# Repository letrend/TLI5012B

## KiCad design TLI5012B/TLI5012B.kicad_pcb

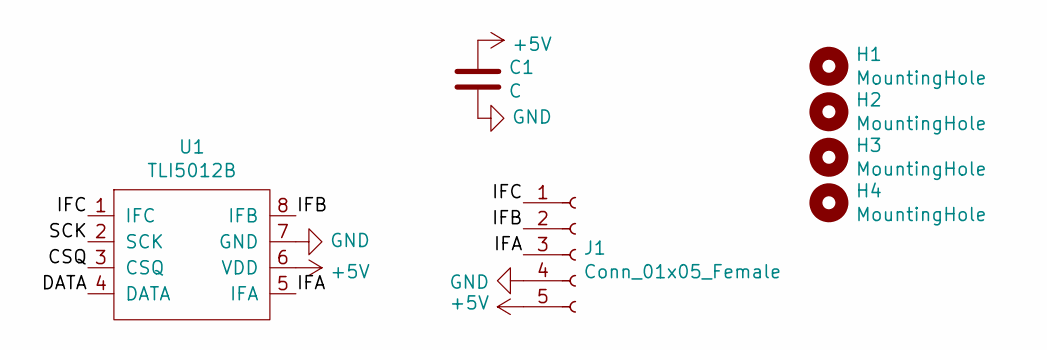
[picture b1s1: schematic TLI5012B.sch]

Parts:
C1: C; C_0402_1005Metric
H1, H2, H3, H4: MountingHole; MountingHole_3.2mm_M3
J1: Conn_01x05_Female; PinHeader_1x05_P1.27mm_Vertical
U1: TLI5012B

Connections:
+5V: C1.1, J1.5, U1.6 (VDD)
/CSQ: U1.3 (CSQ)
/DATA: U1.4 (DATA)
/IFA: J1.3, U1.5 (IFA)
/IFB: J1.2, U1.8 (IFB)
/IFC: J1.1, U1.1 (IFC)
/SCK: U1.2 (SCK)
GND: C1.2, J1.4, U1.7 (GND)

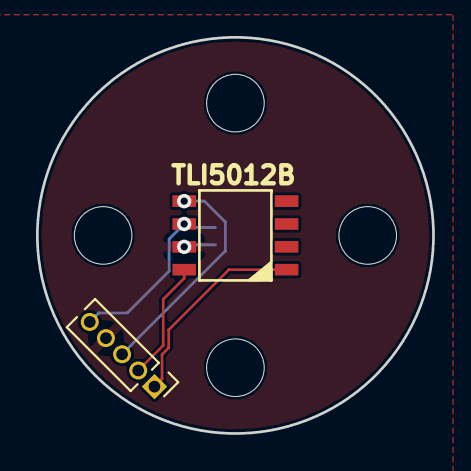
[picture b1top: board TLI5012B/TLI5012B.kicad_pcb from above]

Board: 2 copper layers, 22.0 x 22.0 mm, 7 parts (1 on the bottom side), 5 nets.

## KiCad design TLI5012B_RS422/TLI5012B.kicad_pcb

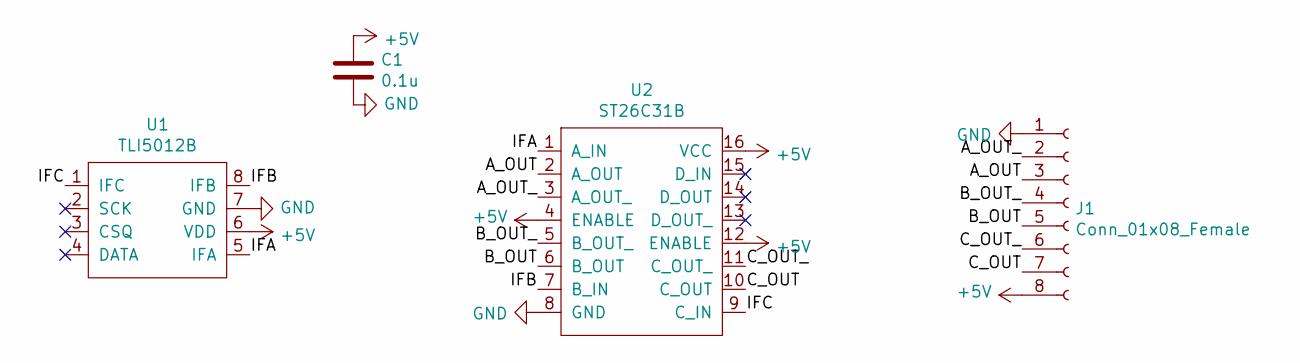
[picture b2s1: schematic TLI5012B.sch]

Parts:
C1: 0.1u; C_0402_1005Metric
J1: Conn_01x08_Female; PinHeader_1x08_P1.27mm_Horizontal
U1: TLI5012B; SO-8_5.3x6.2mm_P1.27mm
U2: ST26C31B; TSSOP-16_4.4x5mm_P0.65mm

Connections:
+5V: C1.1, J1.8, U1.6 (VDD), U2.4 (ENABLE), U2.12 (ENABLE), U2.16 (VCC)
/A_OUT: J1.3, U2.2 (A_OUT)
/A_OUT_: J1.2, U2.3 (A_OUT_)
/B_OUT: J1.5, U2.6 (B_OUT)
/B_OUT_: J1.4, U2.5 (B_OUT_)
/C_OUT: J1.7, U2.10 (C_OUT)
/C_OUT_: J1.6, U2.11 (C_OUT_)
/IFA: U1.5 (IFA), U2.1 (A_IN)
/IFB: U1.8 (IFB), U2.7 (B_IN)
/IFC: U1.1 (IFC), U2.9 (C_IN)
GND: C1.2, J1.1, U1.7 (GND), U2.8 (GND)

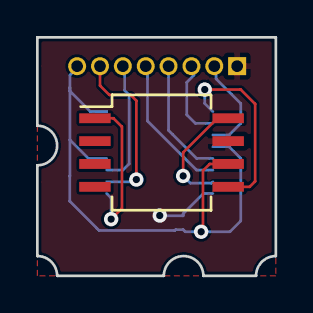
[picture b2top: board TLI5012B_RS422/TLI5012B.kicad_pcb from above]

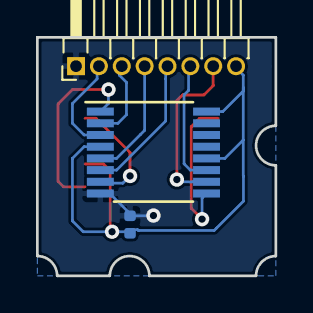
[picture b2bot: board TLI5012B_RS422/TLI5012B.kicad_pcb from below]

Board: 2 copper layers, 13.2 x 13.2 mm, 4 parts (3 on the bottom side), 11 nets.

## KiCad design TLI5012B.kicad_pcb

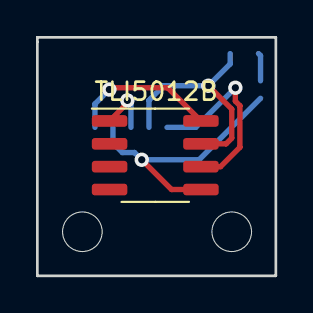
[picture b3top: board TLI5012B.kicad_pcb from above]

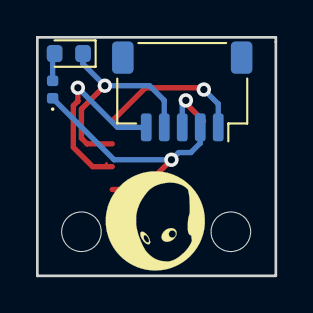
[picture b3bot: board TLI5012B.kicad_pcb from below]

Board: 2 copper layers, 13.2 x 13.2 mm, 4 parts (3 on the bottom side), 6 nets.

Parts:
D1: LED; LED_0603_1608Metric
J1: Conn_01x05_Female; JST_SH_SM05B-SRSS-TB_1x05-1MP_P1.00mm_Horizontal
R1: 1k; LED_0402_1005Metric
U1: TLI5012B; SOP-8_3.76x4.96mm_P1.27mm

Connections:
/GND: D1.1, J1.4, U1.7
/IFA: J1.2, R1.1, U1.5
/IFB: J1.1, U1.8
/IFC: J1.3, U1.1
/VDD: J1.5, U1.6
unnamed: D1.2, R1.2

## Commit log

2019-07-24 initial
2019-07-24 smaller footprint fits better
2019-07-25 with jst connector
2019-07-25 pcbway order submitted
2019-07-29 with single sided
2019-08-02 with mounting holes
2020-01-14 moved to separate folder
2020-01-14 tli with differential driver
2020-10-08 with pcb for walkera_wk-ws-028-014A
2020-10-08 with 1.27 pitch
2020-11-08 with step
